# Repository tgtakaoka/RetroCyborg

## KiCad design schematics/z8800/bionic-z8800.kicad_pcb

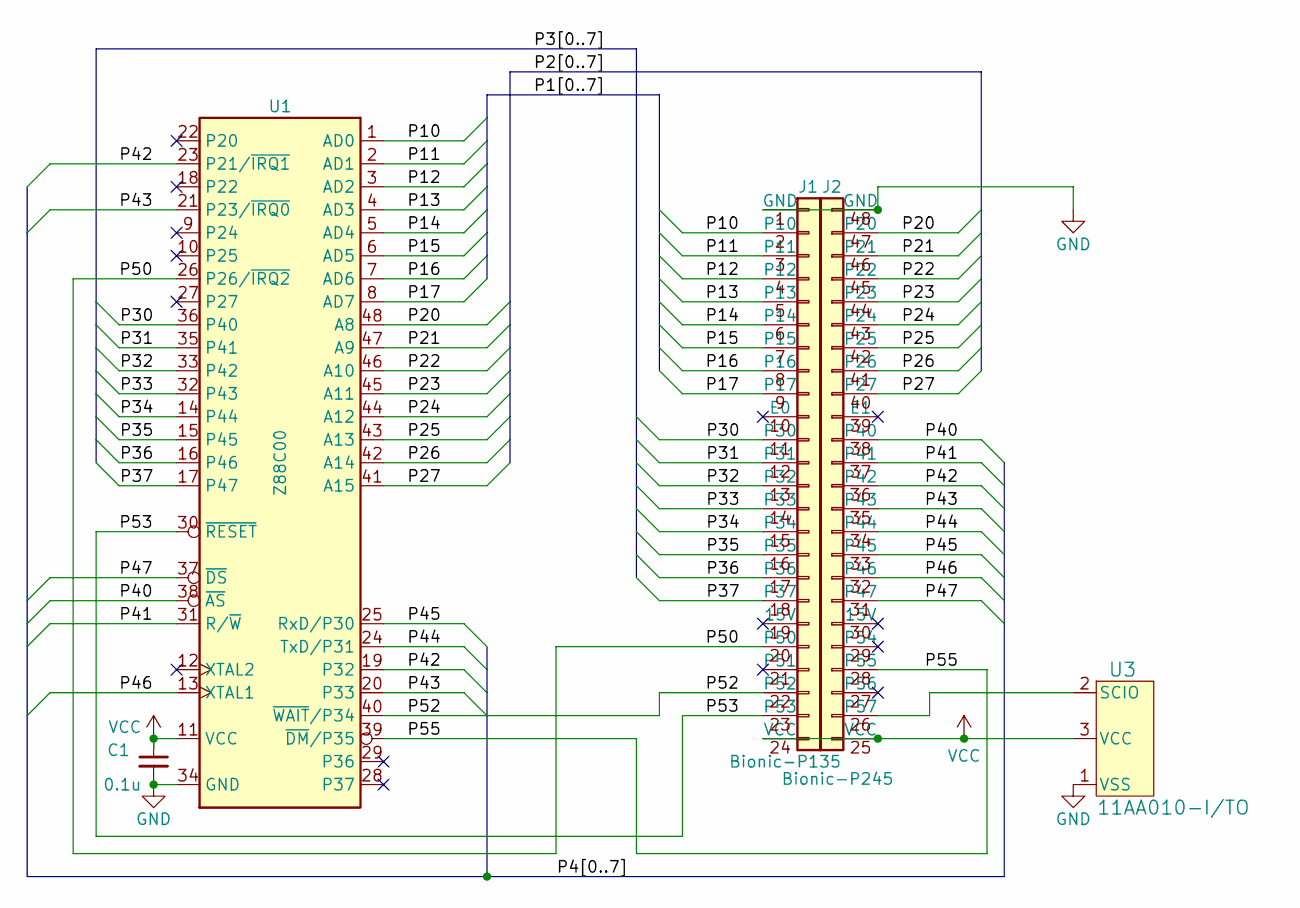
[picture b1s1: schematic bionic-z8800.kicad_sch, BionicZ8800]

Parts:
C1: 0.1u; C_Disc_D3.4mm_W2.1mm_P2.50mm
J1: Bionic-P135; Bionic-P135_Vertical
J2: Bionic-P245; Bionic-P245_Vertical
U1: Z88C00; DIP-48_W15.24mm
U3: 11AA010-I/TO; TO-92_MC_MCH

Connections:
/P10: J1.2 (P10), U1.1 (AD0)
/P11: J1.3 (P11), U1.2 (AD1)
/P12: J1.4 (P12), U1.3 (AD2)
/P13: J1.5 (P13), U1.4 (AD3)
/P14: J1.6 (P14), U1.5 (AD4)
/P15: J1.7 (P15), U1.6 (AD5)
/P16: J1.8 (P16), U1.7 (AD6)
/P17: J1.9 (P17), U1.8 (AD7)
/P20: J2.47 (P20), U1.48 (A8)
/P21: J2.46 (P21), U1.47 (A9)
/P22: J2.45 (P22), U1.46 (A10)
/P23: J2.44 (P23), U1.45 (A11)
/P24: J2.43 (P24), U1.44 (A12)
/P25: J2.42 (P25), U1.43 (A13)
/P26: J2.41 (P26), U1.42 (A14)
/P27: J2.40 (P27), U1.41 (A15)
/P30: J1.11 (P30), U1.36 (P40)
/P31: J1.12 (P31), U1.35 (P41)
/P32: J1.13 (P32), U1.33 (P42)
/P33: J1.14 (P33), U1.32 (P43)
/P34: J1.15 (P34), U1.14 (P44)
/P35: J1.16 (P35), U1.15 (P45)
/P36: J1.17 (P36), U1.16 (P46)
/P37: J1.18 (P37), U1.17 (P47)
/P40: J2.38 (P40), U1.38 (~AS)
/P41: J2.37 (P41), U1.31 (R/~W)
/P42: J2.36 (P42), U1.19 (P32), U1.23 (P21/~IRQ1)
/P43: J2.35 (P43), U1.20 (P33), U1.21 (P23/~IRQ0)
/P44: J2.34 (P44), U1.24 (TxD/P31)
/P45: J2.33 (P45), U1.25 (RxD/P30)
/P46: J2.32 (P46), U1.13 (XTAL1)
/P47: J2.31 (P47), U1.37 (~DS)
/P50: J1.20 (P50), U1.26 (P26/~IRQ2)
/P52: J1.22 (P52), U1.40 (~WAIT/P34)
/P53: J1.23 (P53), U1.30 (~RESET)
/P55: J2.28 (P55), U1.39 (~DM/P35)
GND: C1.2, J1.1 (GND), J2.48 (GND), U1.34 (GND), U3.1 (VSS)
unnamed: J2.26 (P57), U3.2 (SCIO)
VCC: C1.1, J1.24 (VCC), J2.25 (VCC), U1.11 (VCC), U3.3 (VCC)

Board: 2 copper layers, 9 parts (0 on the bottom side), 39 nets, no tracks yet.

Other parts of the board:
MH1, MH2, MH3, MH4: MountingHole_3.2mm_M3

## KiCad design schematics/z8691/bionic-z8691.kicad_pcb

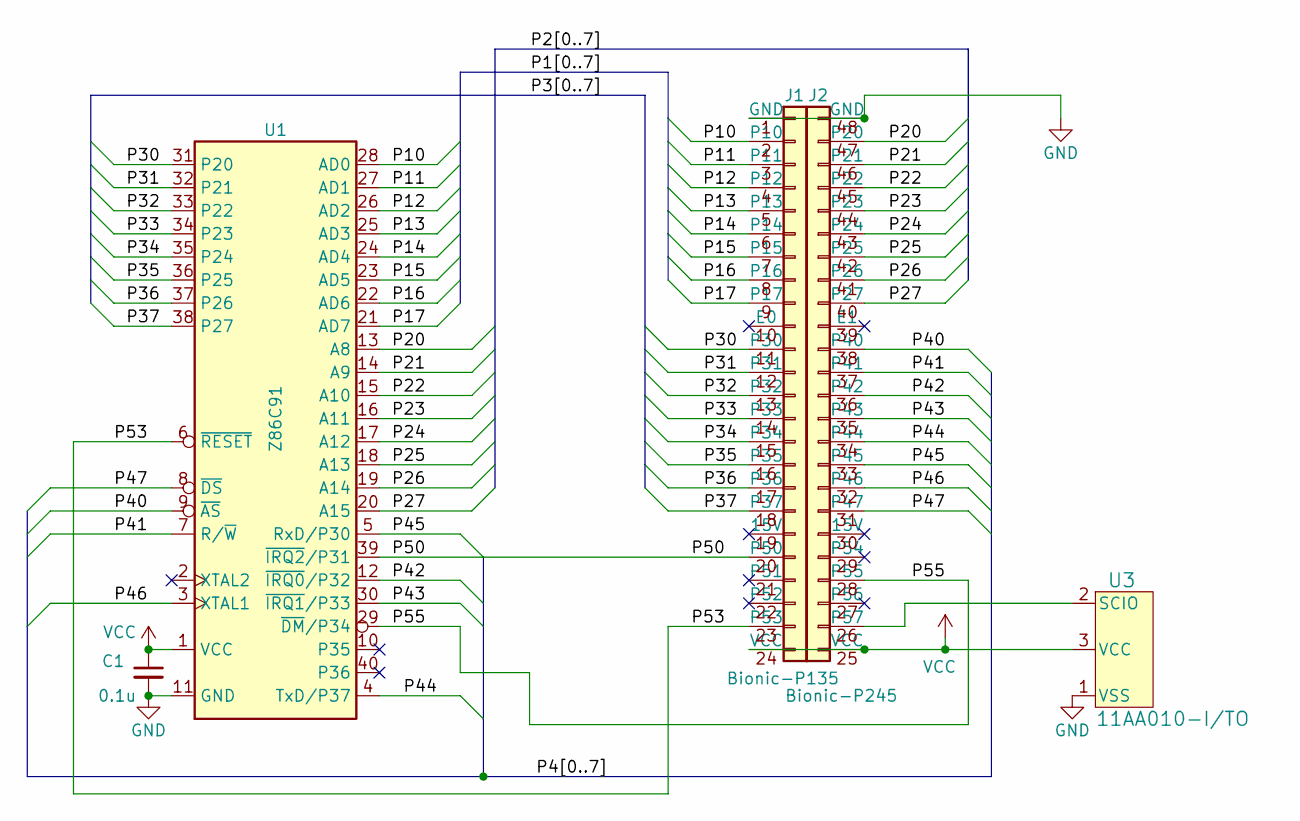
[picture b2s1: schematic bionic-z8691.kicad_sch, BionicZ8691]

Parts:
C1: 0.1u; C_Disc_D3.4mm_W2.1mm_P2.50mm
J1: Bionic-P135; Bionic-P135_Vertical
J2: Bionic-P245; Bionic-P245_Vertical
U1: Z86C91; DIP-40_W15.24mm
U3: 11AA010-I/TO; TO-92_MC_MCH

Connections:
/P10: J1.2 (P10), U1.28 (AD0)
/P11: J1.3 (P11), U1.27 (AD1)
/P12: J1.4 (P12), U1.26 (AD2)
/P13: J1.5 (P13), U1.25 (AD3)
/P14: J1.6 (P14), U1.24 (AD4)
/P15: J1.7 (P15), U1.23 (AD5)
/P16: J1.8 (P16), U1.22 (AD6)
/P17: J1.9 (P17), U1.21 (AD7)
/P20: J2.47 (P20), U1.13 (A8)
/P21: J2.46 (P21), U1.14 (A9)
/P22: J2.45 (P22), U1.15 (A10)
/P23: J2.44 (P23), U1.16 (A11)
/P24: J2.43 (P24), U1.17 (A12)
/P25: J2.42 (P25), U1.18 (A13)
/P26: J2.41 (P26), U1.19 (A14)
/P27: J2.40 (P27), U1.20 (A15)
/P30: J1.11 (P30), U1.31 (P20)
/P31: J1.12 (P31), U1.32 (P21)
/P32: J1.13 (P32), U1.33 (P22)
/P33: J1.14 (P33), U1.34 (P23)
/P34: J1.15 (P34), U1.35 (P24)
/P35: J1.16 (P35), U1.36 (P25)
/P36: J1.17 (P36), U1.37 (P26)
/P37: J1.18 (P37), U1.38 (P27)
/P40: J2.38 (P40), U1.9 (~AS)
/P41: J2.37 (P41), U1.7 (R/~W)
/P42: J2.36 (P42), U1.12 (~IRQ0/P32)
/P43: J2.35 (P43), U1.30 (~IRQ1/P33)
/P44: J2.34 (P44), U1.4 (TxD/P37)
/P45: J2.33 (P45), U1.5 (RxD/P30)
/P46: J2.32 (P46), U1.3 (XTAL1)
/P47: J2.31 (P47), U1.8 (~DS)
/P50: J1.20 (P50), U1.39 (~IRQ2/P31)
/P53: J1.23 (P53), U1.6 (~RESET)
/P55: J2.28 (P55), U1.29 (~DM/P34)
GND: C1.2, J1.1 (GND), J2.48 (GND), U1.11 (GND), U3.1 (VSS)
unnamed: J2.26 (P57), U3.2 (SCIO)
VCC: C1.1, J1.24 (VCC), J2.25 (VCC), U1.1 (VCC), U3.3 (VCC)

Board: 2 copper layers, 9 parts (0 on the bottom side), 38 nets, no tracks yet.

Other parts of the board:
MH1, MH2, MH3, MH4: MountingHole_3.2mm_M3

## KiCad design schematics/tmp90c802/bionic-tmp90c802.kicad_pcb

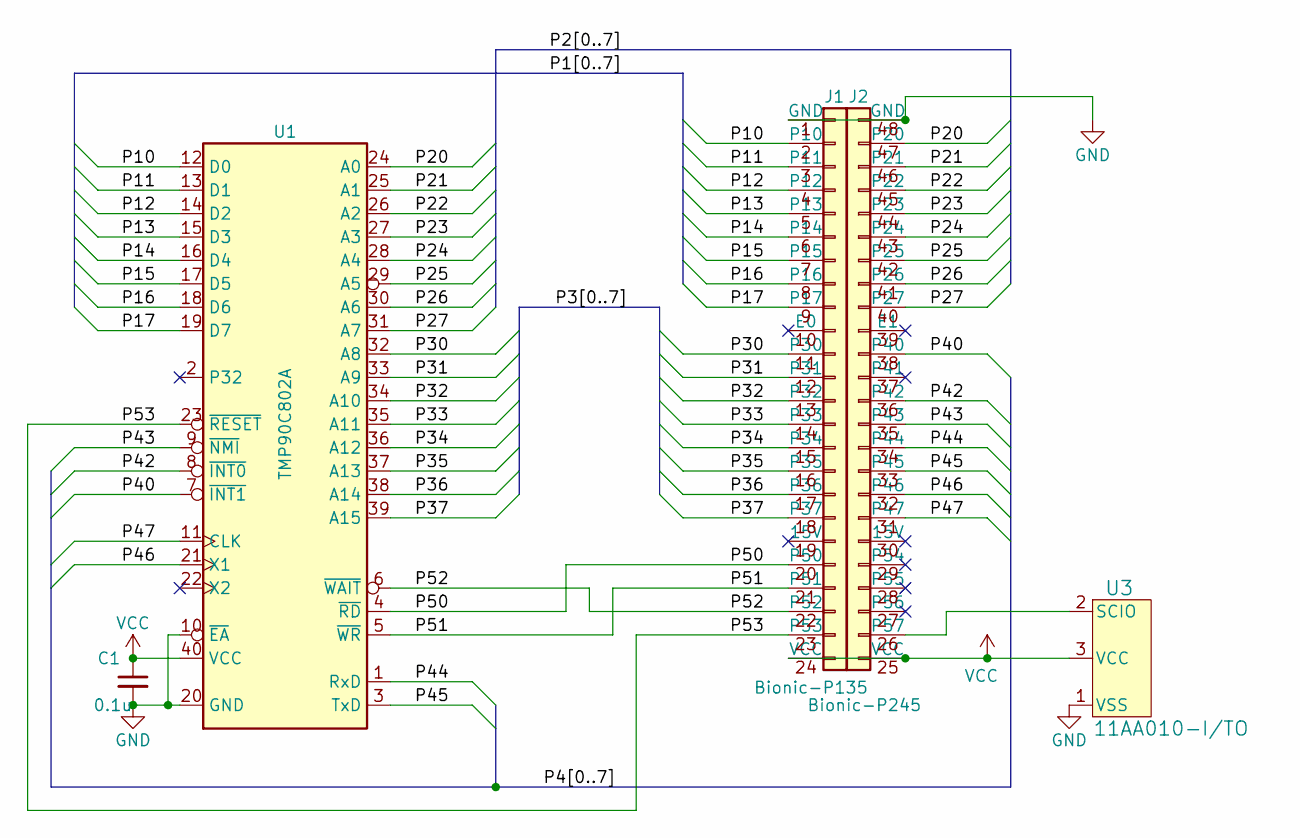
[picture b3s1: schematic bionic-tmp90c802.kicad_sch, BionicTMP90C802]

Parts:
C1: 0.1u; C_Disc_D3.4mm_W2.1mm_P2.50mm
J1: Bionic-P135; Bionic-P135_Vertical
J2: Bionic-P245; Bionic-P245_Vertical
U1: TMP90C802A; DIP-40_W15.24mm
U3: 11AA010-I/TO; TO-92_MC_MCH

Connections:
/P10: J1.2 (P10), U1.12 (D0)
/P11: J1.3 (P11), U1.13 (D1)
/P12: J1.4 (P12), U1.14 (D2)
/P13: J1.5 (P13), U1.15 (D3)
/P14: J1.6 (P14), U1.16 (D4)
/P15: J1.7 (P15), U1.17 (D5)
/P16: J1.8 (P16), U1.18 (D6)
/P17: J1.9 (P17), U1.19 (D7)
/P20: J2.47 (P20), U1.24 (A0)
/P21: J2.46 (P21), U1.25 (A1)
/P22: J2.45 (P22), U1.26 (A2)
/P23: J2.44 (P23), U1.27 (A3)
/P24: J2.43 (P24), U1.28 (A4)
/P25: J2.42 (P25), U1.29 (A5)
/P26: J2.41 (P26), U1.30 (A6)
/P27: J2.40 (P27), U1.31 (A7)
/P30: J1.11 (P30), U1.32 (A8)
/P31: J1.12 (P31), U1.33 (A9)
/P32: J1.13 (P32), U1.34 (A10)
/P33: J1.14 (P33), U1.35 (A11)
/P34: J1.15 (P34), U1.36 (A12)
/P35: J1.16 (P35), U1.37 (A13)
/P36: J1.17 (P36), U1.38 (A14)
/P37: J1.18 (P37), U1.39 (A15)
/P40: J2.38 (P40), U1.7 (~INT1)
/P42: J2.36 (P42), U1.8 (~INT0)
/P43: J2.35 (P43), U1.9 (~NMI)
/P44: J2.34 (P44), U1.1 (RxD)
/P45: J2.33 (P45), U1.3 (TxD)
/P46: J2.32 (P46), U1.21 (X1)
/P47: J2.31 (P47), U1.11 (CLK)
/P50: J1.20 (P50), U1.4 (~RD)
/P51: J1.21 (P51), U1.5 (~WR)
/P52: J1.22 (P52), U1.6 (~WAIT)
/P53: J1.23 (P53), U1.23 (~RESET)
GND: C1.2, J1.1 (GND), J2.48 (GND), U1.10 (~EA), U1.20 (GND), U3.1 (VSS)
unnamed: J2.26 (P57), U3.2 (SCIO)
VCC: C1.1, J1.24 (VCC), J2.25 (VCC), U1.40 (VCC), U3.3 (VCC)

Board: 2 copper layers, 9 parts (0 on the bottom side), 38 nets, no tracks yet.

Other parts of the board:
MH1, MH2, MH3, MH4: MountingHole_3.2mm_M3

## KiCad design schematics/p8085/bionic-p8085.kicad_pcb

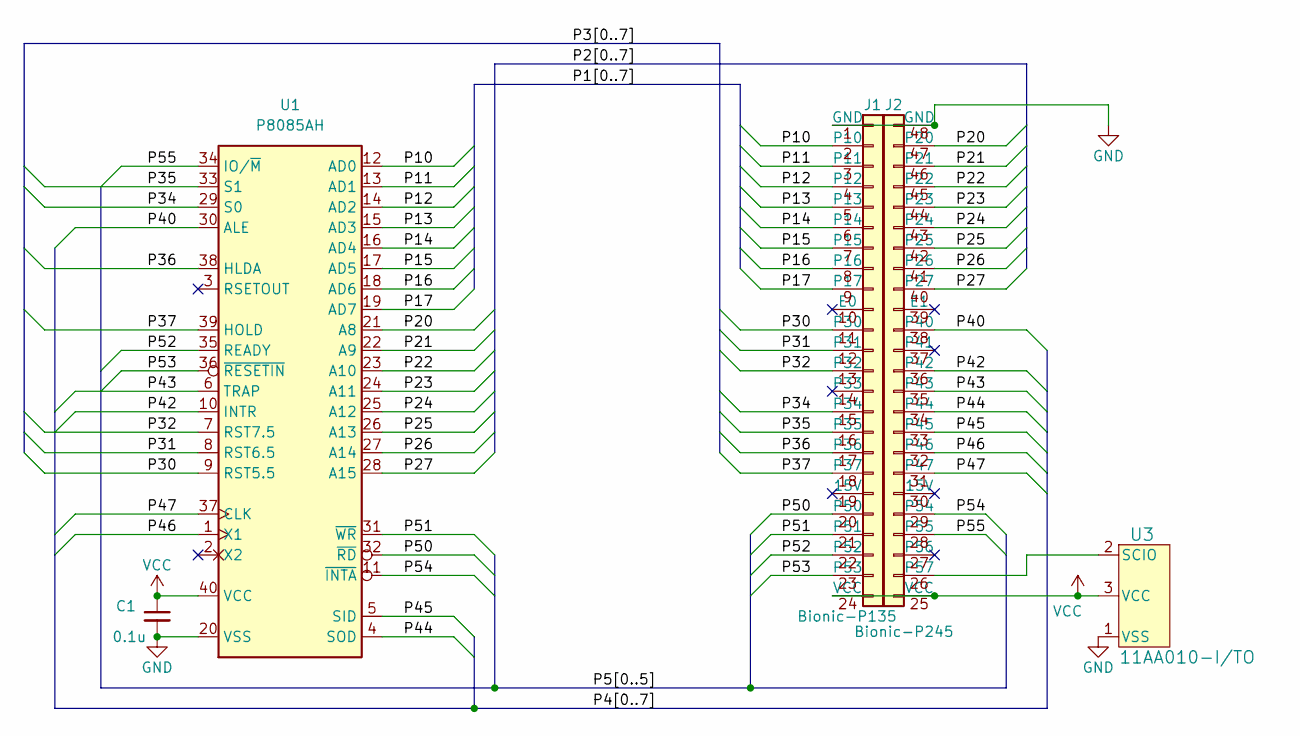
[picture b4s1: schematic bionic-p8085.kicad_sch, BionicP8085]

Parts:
C1: 0.1u; C_Disc_D3.4mm_W2.1mm_P2.50mm
J1: Bionic-P135; Bionic-P135_Vertical
J2: Bionic-P245; Bionic-P245_Vertical
U1: P8085AH; DIP-40_W15.24mm
U3: 11AA010-I/TO; TO-92_MC_MCH

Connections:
/P10: J1.2 (P10), U1.12 (AD0)
/P11: J1.3 (P11), U1.13 (AD1)
/P12: J1.4 (P12), U1.14 (AD2)
/P13: J1.5 (P13), U1.15 (AD3)
/P14: J1.6 (P14), U1.16 (AD4)
/P15: J1.7 (P15), U1.17 (AD5)
/P16: J1.8 (P16), U1.18 (AD6)
/P17: J1.9 (P17), U1.19 (AD7)
/P20: J2.47 (P20), U1.21 (A8)
/P21: J2.46 (P21), U1.22 (A9)
/P22: J2.45 (P22), U1.23 (A10)
/P23: J2.44 (P23), U1.24 (A11)
/P24: J2.43 (P24), U1.25 (A12)
/P25: J2.42 (P25), U1.26 (A13)
/P26: J2.41 (P26), U1.27 (A14)
/P27: J2.40 (P27), U1.28 (A15)
/P30: J1.11 (P30), U1.9 (RST5.5)
/P31: J1.12 (P31), U1.8 (RST6.5)
/P32: J1.13 (P32), U1.7 (RST7.5)
/P34: J1.15 (P34), U1.29 (S0)
/P35: J1.16 (P35), U1.33 (S1)
/P36: J1.17 (P36), U1.38 (HLDA)
/P37: J1.18 (P37), U1.39 (HOLD)
/P40: J2.38 (P40), U1.30 (ALE)
/P42: J2.36 (P42), U1.10 (INTR)
/P43: J2.35 (P43), U1.6 (TRAP)
/P44: J2.34 (P44), U1.4 (SOD)
/P45: J2.33 (P45), U1.5 (SID)
/P46: J2.32 (P46), U1.1 (X1)
/P47: J2.31 (P47), U1.37 (CLK)
/P50: J1.20 (P50), U1.32 (~RD)
/P51: J1.21 (P51), U1.31 (~WR)
/P52: J1.22 (P52), U1.35 (READY)
/P53: J1.23 (P53), U1.36 (~RESETIN)
/P54: J2.29 (P54), U1.11 (~INTA)
/P55: J2.28 (P55), U1.34 (IO/~M)
GND: C1.2, J1.1 (GND), J2.48 (GND), U1.20 (VSS), U3.1 (VSS)
unnamed: J2.26 (P57), U3.2 (SCIO)
VCC: C1.1, J1.24 (VCC), J2.25 (VCC), U1.40 (VCC), U3.3 (VCC)

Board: 2 copper layers, 9 parts (0 on the bottom side), 39 nets, no tracks yet.

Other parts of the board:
MH1, MH2, MH3, MH4: MountingHole_3.2mm_M3

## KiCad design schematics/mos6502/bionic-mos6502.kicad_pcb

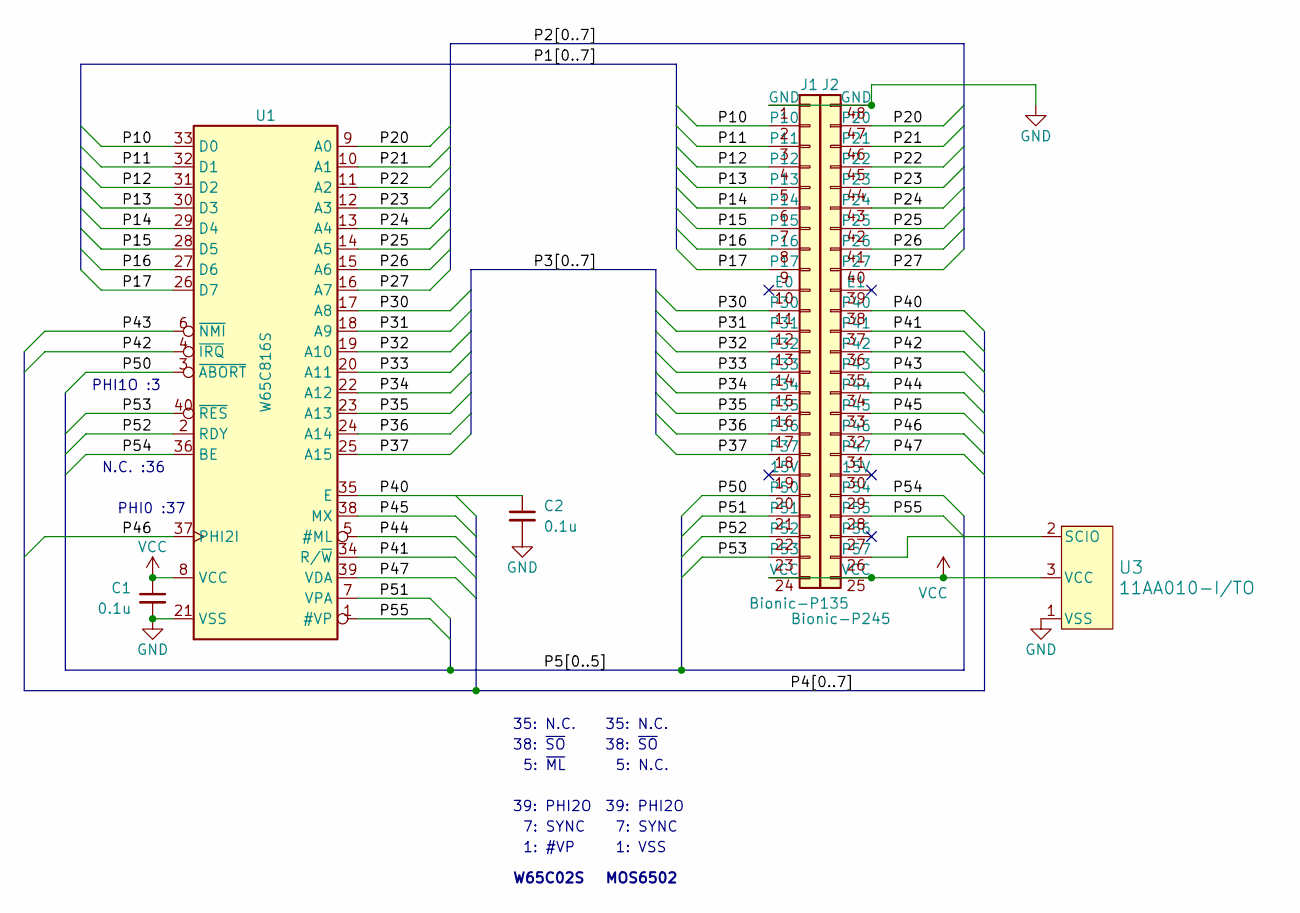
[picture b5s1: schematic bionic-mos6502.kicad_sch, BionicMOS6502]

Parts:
C1, C2: 0.1u; C_Disc_D3.4mm_W2.1mm_P2.50mm
J1: Bionic-P135; Bionic-P135_Vertical
J2: Bionic-P245; Bionic-P245_Vertical
U1: W65C816S; DIP-40_W15.24mm
U3: 11AA010-I/TO; TO-92_MC_MCH

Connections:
/P10: J1.2 (P10), U1.33 (D0)
/P11: J1.3 (P11), U1.32 (D1)
/P12: J1.4 (P12), U1.31 (D2)
/P13: J1.5 (P13), U1.30 (D3)
/P14: J1.6 (P14), U1.29 (D4)
/P15: J1.7 (P15), U1.28 (D5)
/P16: J1.8 (P16), U1.27 (D6)
/P17: J1.9 (P17), U1.26 (D7)
/P20: J2.47 (P20), U1.9 (A0)
/P21: J2.46 (P21), U1.10 (A1)
/P22: J2.45 (P22), U1.11 (A2)
/P23: J2.44 (P23), U1.12 (A3)
/P24: J2.43 (P24), U1.13 (A4)
/P25: J2.42 (P25), U1.14 (A5)
/P26: J2.41 (P26), U1.15 (A6)
/P27: J2.40 (P27), U1.16 (A7)
/P30: J1.11 (P30), U1.17 (A8)
/P31: J1.12 (P31), U1.18 (A9)
/P32: J1.13 (P32), U1.19 (A10)
/P33: J1.14 (P33), U1.20 (A11)
/P34: J1.15 (P34), U1.22 (A12)
/P35: J1.16 (P35), U1.23 (A13)
/P36: J1.17 (P36), U1.24 (A14)
/P37: J1.18 (P37), U1.25 (A15)
/P40: C2.1, J2.38 (P40), U1.35 (E)
/P41: J2.37 (P41), U1.34 (R/~W)
/P42: J2.36 (P42), U1.4 (~IRQ)
/P43: J2.35 (P43), U1.6 (~NMI)
/P44: J2.34 (P44), U1.5 (#ML)
/P45: J2.33 (P45), U1.38 (MX)
/P46: J2.32 (P46), U1.37 (PHI2I)
/P47: J2.31 (P47), U1.39 (VDA)
/P50: J1.20 (P50), U1.3 (~ABORT)
/P51: J1.21 (P51), U1.7 (VPA)
/P52: J1.22 (P52), U1.2 (RDY)
/P53: J1.23 (P53), U1.40 (~RES)
/P54: J2.29 (P54), U1.36 (BE)
/P55: J2.28 (P55), U1.1 (#VP)
GND: C1.2, C2.2, J1.1 (GND), J2.48 (GND), U1.21 (VSS), U3.1 (VSS)
unnamed: J2.26 (P57), U3.2 (SCIO)
VCC: C1.1, J1.24 (VCC), J2.25 (VCC), U1.8 (VCC), U3.3 (VCC)

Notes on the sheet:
N.C. :36
PHI0 :37
35: N.C.
MOS6502
5: N.C.
W65C02S
7: SYNC
PHI1O :3
39: PHI2O
1: VSS
5: ~{ML}
1: #VP
38: ~{SO}

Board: 2 copper layers, 10 parts (0 on the bottom side), 41 nets, no tracks yet.

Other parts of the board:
MH1, MH2, MH3, MH4: MountingHole_3.2mm_M3

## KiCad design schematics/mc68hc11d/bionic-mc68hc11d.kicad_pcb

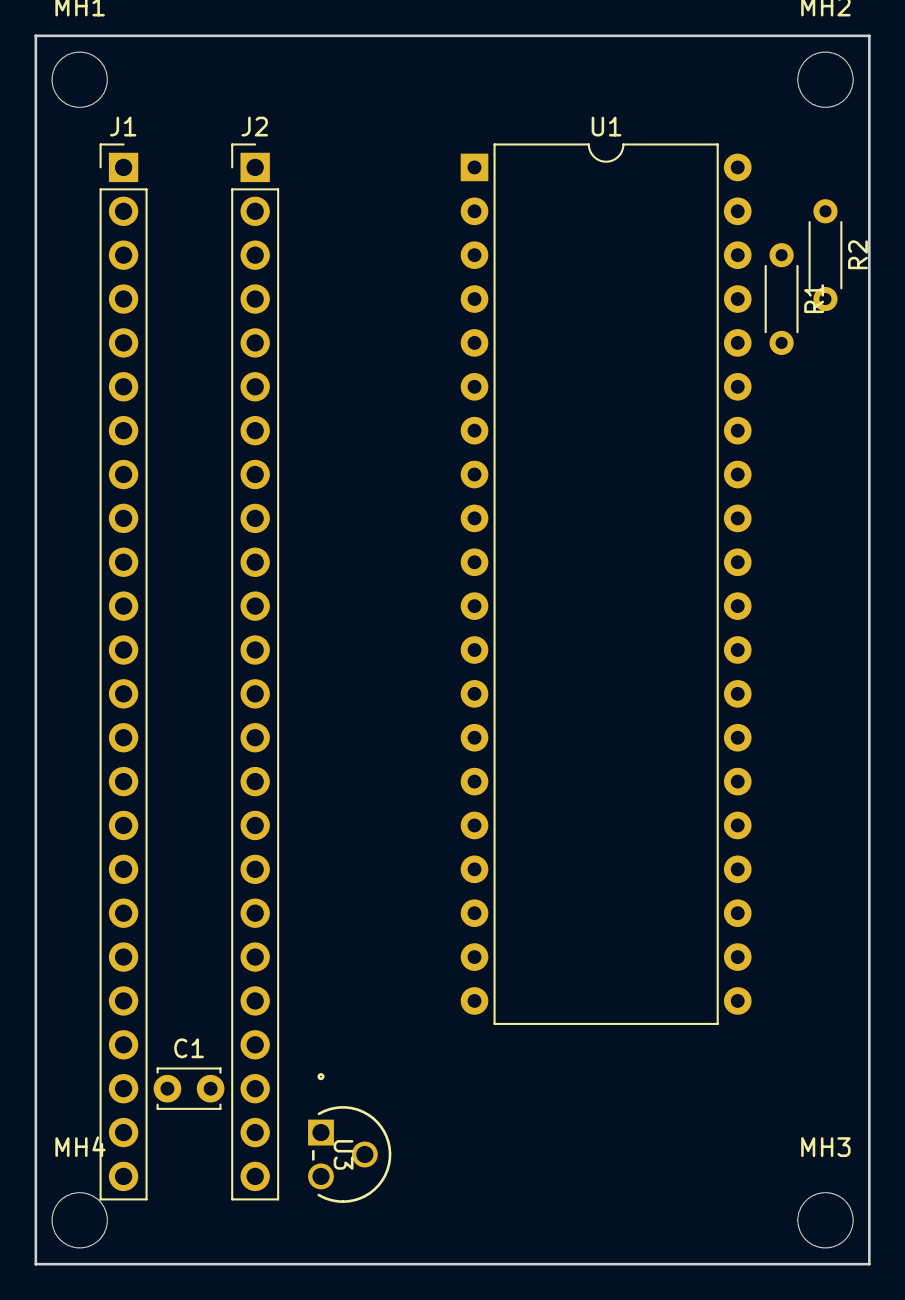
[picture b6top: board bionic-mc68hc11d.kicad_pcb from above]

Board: 2 copper layers, 48.3 x 71.1 mm, 11 parts (0 on the bottom side), 40 nets, no tracks yet.

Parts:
C1: 0.1u; C_Disc_D3.4mm_W2.1mm_P2.50mm
J1: Bionic-P135; Bionic-P135_Vertical
J2: Bionic-P245; Bionic-P245_Vertical
MH1, MH2, MH3, MH4: MountingHole_3.2mm_M3
R1, R2: 10k; R_Axial_DIN0204_L3.6mm_D1.6mm_P5.08mm_Horizontal
U1: MC68HC11D0P; DIP-40_W15.24mm
U3: 11AA010-I/TO; TO-92_MC_MCH

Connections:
/P10: J1.2 (P10), U1.2 (AD0)
/P11: J1.3 (P11), U1.3 (AD1)
/P12: J1.4 (P12), U1.4 (AD2)
/P13: J1.5 (P13), U1.5 (AD3)
/P14: J1.6 (P14), U1.6 (AD4)
/P15: J1.7 (P15), U1.7 (AD5)
/P16: J1.8 (P16), U1.8 (AD6)
/P17: J1.9 (P17), U1.9 (AD7)
/P20: J2.47 (P20), U1.35 (A8)
/P21: J2.46 (P21), U1.34 (A9)
/P22: J2.45 (P22), U1.33 (A10)
/P23: J2.44 (P23), U1.32 (A11)
/P24: J2.43 (P24), U1.31 (A12)
/P25: J2.42 (P25), U1.30 (A13)
/P26: J2.41 (P26), U1.29 (A14)
/P27: J2.40 (P27), U1.28 (A15)
/P30: J1.11 (P30), U1.27 (PA0)
/P31: J1.12 (P31), U1.26 (PA1)
/P32: J1.13 (P32), U1.25 (PA2)
/P33: J1.14 (P33), U1.24 (PA3)
/P34: J1.15 (P34), U1.17 (MISO/PD2)
/P35: J1.16 (P35), U1.18 (MOSI/PD3)
/P36: J1.17 (P36), U1.19 (SCK/PD4)
/P37: J1.18 (P37), U1.20 (~SS/PD5)
/P40: J2.38 (P40), U1.12 (AS)
/P41: J2.37 (P41), U1.11 (R/~W)
/P42: J2.36 (P42), U1.14 (~IRQ)
/P43: J2.35 (P43), U1.10 (~XIRQ)
/P44: J2.34 (P44), U1.16 (TxD/PD1)
/P45: J2.33 (P45), U1.15 (RxD/PD0)
/P46: J2.32 (P46), U1.39 (EXTAL)
/P47: J2.31 (P47), U1.38 (E)
/P50: J1.20 (P50), R2.2, U1.37 (MODA/~LIR)
/P51: J1.21 (P51), R1.2, U1.36 (MODB)
/P53: J1.23 (P53), U1.13 (~RESET)
/P54: J2.29 (P54), U1.23 (PA5)
/P55: J2.28 (P55), U1.22 (PA7)
GND: C1.2, J1.1 (GND), J2.48 (GND), U1.1 (VSS), U3.1 (VSS)
unnamed: J2.26 (P57), U3.2 (SCIO)
VCC: C1.1, J1.24 (VCC), J2.25 (VCC), R1.1, R2.1, U1.21 (VDD), U3.3 (VCC)

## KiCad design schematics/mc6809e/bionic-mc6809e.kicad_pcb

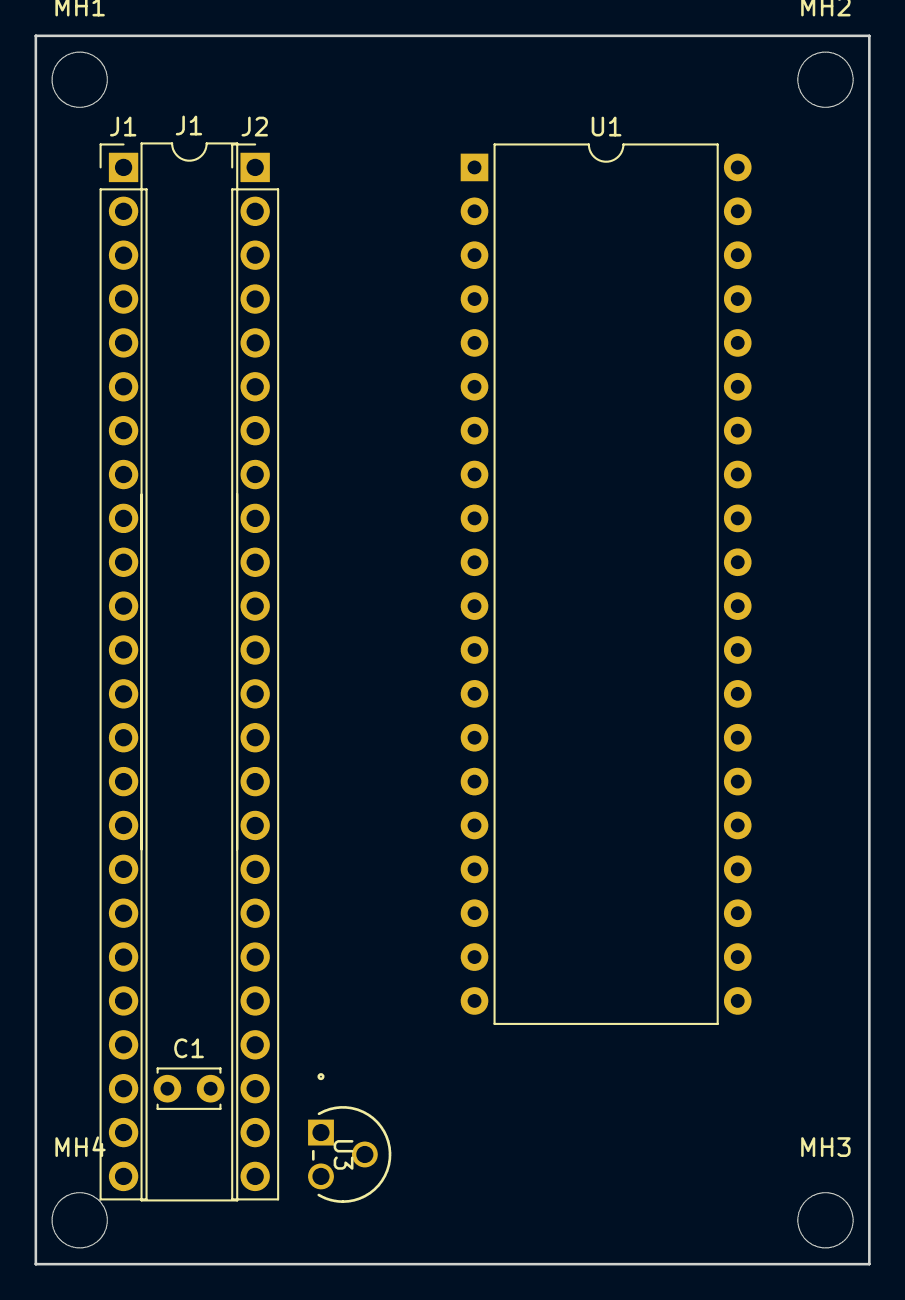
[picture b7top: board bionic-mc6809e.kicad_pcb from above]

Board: 2 copper layers, 48.3 x 71.1 mm, 10 parts (0 on the bottom side), 41 nets, no tracks yet.

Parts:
C1: 0.1u; C_Disc_D3.4mm_W2.1mm_P2.50mm
J1: BionicConnector; DIP-48_W7.62mm
J1#2: Bionic-P135; Bionic-P135_Vertical
J2: Bionic-P245; Bionic-P245_Vertical
MH1, MH2, MH3, MH4: MountingHole_3.2mm_M3
U1: MC6809EP; DIP-40_W15.24mm
U3: 11AA010-I/TO; TO-92_MC_MCH

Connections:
/P10: J1.2 (P10), J1#2.2 (P10), U1.31 (D0)
/P11: J1.3 (P11), J1#2.3 (P11), U1.30 (D1)
/P12: J1.4 (P12), J1#2.4 (P12), U1.29 (D2)
/P13: J1.5 (P13), J1#2.5 (P13), U1.28 (D3)
/P14: J1.6 (P14), J1#2.6 (P14), U1.27 (D4)
/P15: J1.7 (P15), J1#2.7 (P15), U1.26 (D5)
/P16: J1.8 (P16), J1#2.8 (P16), U1.25 (D6)
/P17: J1.9 (P17), J1#2.9 (P17), U1.24 (D7)
/P20: J1.47 (P20), J2.47 (P20), U1.8 (A0)
/P21: J1.46 (P21), J2.46 (P21), U1.9 (A1)
/P22: J1.45 (P22), J2.45 (P22), U1.10 (A2)
/P23: J1.44 (P23), J2.44 (P23), U1.11 (A3)
/P24: J1.43 (P24), J2.43 (P24), U1.12 (A4)
/P25: J1.42 (P25), J2.42 (P25), U1.13 (A5)
/P26: J1.41 (P26), J2.41 (P26), U1.14 (A6)
/P27: J1.40 (P27), J2.40 (P27), U1.15 (A7)
/P30: J1.11 (P30), J1#2.11 (P30), U1.16 (A8)
/P31: J1.12 (P31), J1#2.12 (P31), U1.17 (A9)
/P32: J1.13 (P32), J1#2.13 (P32), U1.18 (A10)
/P33: J1.14 (P33), J1#2.14 (P33), U1.19 (A11)
/P34: J1.15 (P34), J1#2.15 (P34), U1.20 (A12)
/P35: J1.16 (P35), J1#2.16 (P35), U1.21 (A13)
/P36: J1.17 (P36), J1#2.17 (P36), U1.22 (A14)
/P37: J1.18 (P37), J1#2.18 (P37), U1.23 (A15)
/P40: J1.38 (P40), J2.38 (P40), U1.40 (~HALT)
/P41: J1.37 (P41), J2.37 (P41), U1.32 (R/~W)
/P42: J1.36 (P42), J2.36 (P42), U1.3 (~IRQ)
/P43: J1.35 (P43), J2.35 (P43), U1.2 (~NMI)
/P44: J1.34 (P44), J2.34 (P44), U1.33 (BUSY)
/P45: J1.33 (P45), J2.33 (P45), U1.4 (~FIRQ)
/P46: J1.32 (P46), J2.32 (P46), U1.34 (E)
/P47: J1.31 (P47), J2.31 (P47), U1.35 (Q)
/P50: J1.20 (P50), J1#2.20 (P50), U1.36 (AVMA)
/P51: J1.21 (P51), J1#2.21 (P51), U1.5 (BS)
/P52: J1.22 (P52), J1#2.22 (P52), U1.38 (LIC)
/P53: J1.23 (P53), J1#2.23 (P53), U1.37 (~RESET)
/P54: J1.29 (P54), J2.29 (P54), U1.39 (TSC)
/P55: J1.28 (P55), J2.28 (P55), U1.6 (BA)
GND: C1.2, J1.1 (GND), J1.48 (GND), J1#2.1 (GND), J2.48 (GND), U1.1 (VSS), U3.1 (VSS)
unnamed: J2.26 (P57), U3.2 (SCIO)
VCC: C1.1, J1.24 (VCC), J1.25 (VCC), J1#2.24 (VCC), J2.25 (VCC), U1.7 (VCC), U3.3 (VCC)

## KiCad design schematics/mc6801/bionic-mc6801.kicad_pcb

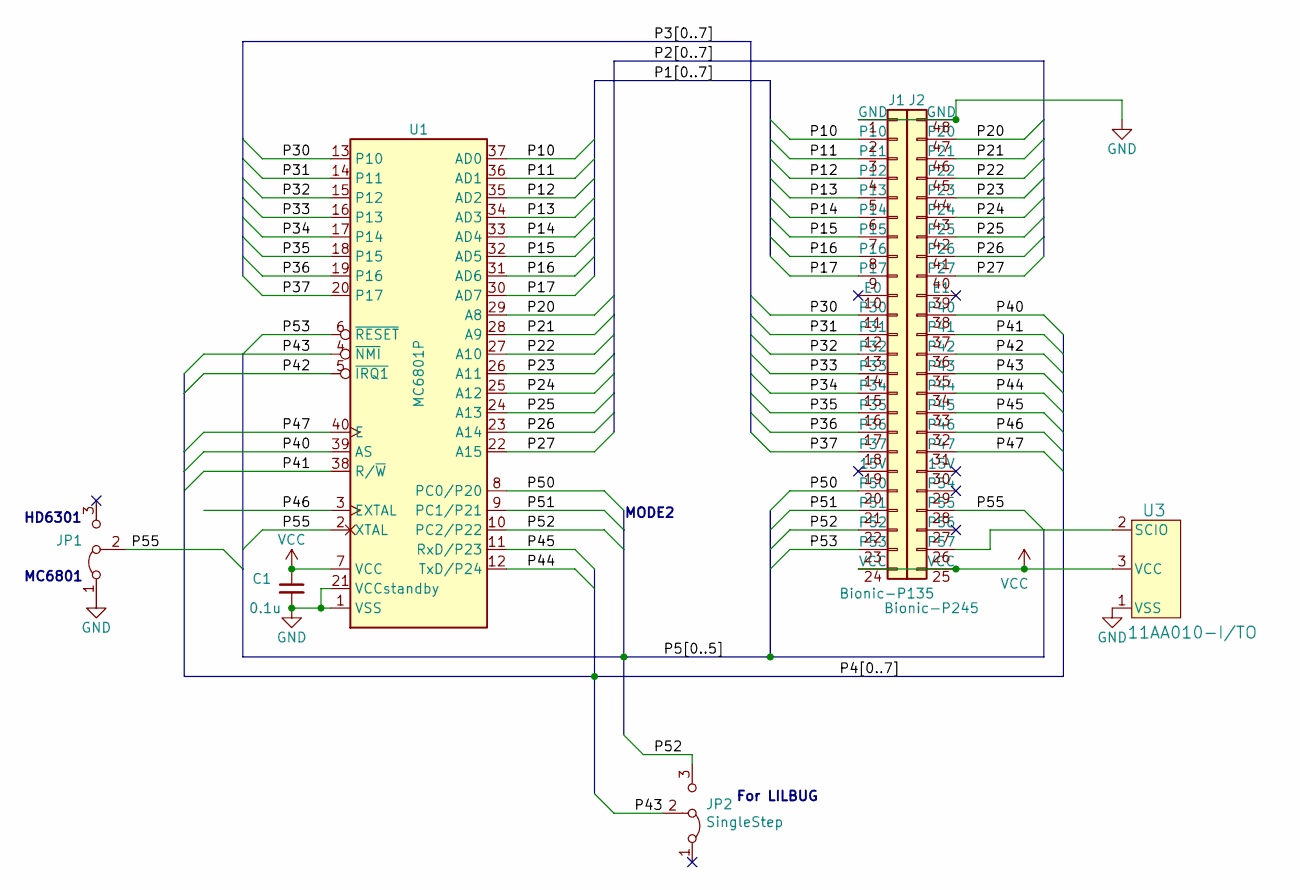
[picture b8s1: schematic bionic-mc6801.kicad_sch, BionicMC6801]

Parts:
C1: 0.1u; C_Disc_D3.4mm_W2.1mm_P2.50mm
J1: Bionic-P135; Bionic-P135_Vertical
J2: Bionic-P245; Bionic-P245_Vertical
JP1: MC6801; PinHeader_1x03_P2.54mm_Vertical
JP2: SingleStep; PinHeader_1x03_P2.54mm_Vertical
U1: MC6801P; DIP-40_W15.24mm
U3: 11AA010-I/TO; TO-92_MC_MCH

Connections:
/P10: J1.2 (P10), U1.37 (AD0)
/P11: J1.3 (P11), U1.36 (AD1)
/P12: J1.4 (P12), U1.35 (AD2)
/P13: J1.5 (P13), U1.34 (AD3)
/P14: J1.6 (P14), U1.33 (AD4)
/P15: J1.7 (P15), U1.32 (AD5)
/P16: J1.8 (P16), U1.31 (AD6)
/P17: J1.9 (P17), U1.30 (AD7)
/P20: J2.47 (P20), U1.29 (A8)
/P21: J2.46 (P21), U1.28 (A9)
/P22: J2.45 (P22), U1.27 (A10)
/P23: J2.44 (P23), U1.26 (A11)
/P24: J2.43 (P24), U1.25 (A12)
/P25: J2.42 (P25), U1.24 (A13)
/P26: J2.41 (P26), U1.23 (A14)
/P27: J2.40 (P27), U1.22 (A15)
/P30: J1.11 (P30), U1.13 (P10)
/P31: J1.12 (P31), U1.14 (P11)
/P32: J1.13 (P32), U1.15 (P12)
/P33: J1.14 (P33), U1.16 (P13)
/P34: J1.15 (P34), U1.17 (P14)
/P35: J1.16 (P35), U1.18 (P15)
/P36: J1.17 (P36), U1.19 (P16)
/P37: J1.18 (P37), U1.20 (P17)
/P40: J2.38 (P40), U1.39 (AS)
/P41: J2.37 (P41), U1.38 (R/~W)
/P42: J2.36 (P42), U1.5 (~IRQ1)
/P43: J2.35 (P43), JP2.2 (C), U1.4 (~NMI)
/P44: J2.34 (P44), U1.12 (TxD/P24)
/P45: J2.33 (P45), U1.11 (RxD/P23)
/P46: J2.32 (P46), U1.3 (EXTAL)
/P47: J2.31 (P47), U1.40 (E)
/P50: J1.20 (P50), U1.8 (PC0/P20)
/P51: J1.21 (P51), U1.9 (PC1/P21)
/P52: J1.22 (P52), JP2.3 (B), U1.10 (PC2/P22)
/P53: J1.23 (P53), U1.6 (~RESET)
/P55: J2.28 (P55), JP1.2 (C), U1.2 (XTAL)
GND: C1.2, J1.1 (GND), J2.48 (GND), JP1.1 (A), U1.1 (VSS), U1.21 (VCCstandby), U3.1 (VSS)
unnamed: J2.26 (P57), U3.2 (SCIO)
VCC: C1.1, J1.24 (VCC), J2.25 (VCC), U1.7 (VCC), U3.3 (VCC)

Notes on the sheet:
MODE2
For LILBUG
HD6301
MC6801

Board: 2 copper layers, 11 parts (0 on the bottom side), 40 nets, no tracks yet.

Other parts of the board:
MH1, MH2, MH3, MH4: MountingHole_3.2mm_M3

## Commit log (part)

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2021-10-28 [HD6309E] Update Arduino IDE setting comment
2021-10-28 Add retro CPU's pin out
    - CDP1802
    - HD6301V/HD6303R
    - INS8060
    - INS8070
    - MC68008P
    - MC6800
2021-10-28 [CyborgZ84C00] update libcli 1.0.3
2021-10-28 [CyborgHD6309E] update libcli 1.0.3
2021-10-28 Add PlatformIO configurations
2021-10-28 Restore CyborgHD6309E/Prototype3 code
2021-10-28 Add NSC800N pin out
    NSC800N has Z80 software architecture and 8051-like hardware signals.
2021-10-28 Add MC6802/MC6808 pin out
2021-10-28 [CyborgZ84C00] update debugger code
2021-10-28 [CyborgHD6309E] Prototype3 modify pins map
2021-10-28 [CyborgHD6309E] Add debug status to Signals
2021-10-28 [CyborgHD6309E] Consolidate Prototype3/4 debugger
2021-10-28 [CyborgHD6309E] Prorotype5 debugger
2021-10-28 [CyborgHD6309E] Add Signals.advancedValidMemoryAddress
2021-10-28 [BionicHD6303] Add clock generator test running on Teensy 3.5
2021-10-28 [CyborgHD6309E] Reorganize Prototype4
2021-10-28 [CyborgHD6309E] Fix register endian handling
    Values in captured buffer from stack frame is little endian which is
    accidentally equals to AVR's endianess.
2021-10-28 [CyborgHD6309E] Refactor Pins.cycle()
    Now HD6309's native mode works correctly.
2021-10-28 [CyborgZ84C00] Update pin mapping
2021-10-28 [CyborgHD6309E] Consolidate Pins.execInst/captureReads/captureWrites
2021-10-28 [CyborgHD6309E] Add Prototype5 cgen6309e-test
2021-10-28 Add DIP definitions
    This TOML files are input for
    https://github.com/tgtakaoka/dip
2021-10-28 [CyborgZ84C00] Add cgenz80-test
2021-10-28 [CyborgHD6309E] Batch capture and print
2021-10-28 Add Teensy 3.5/4.1, Nano Every pin out
2021-10-28 [CyborgHD6309E] Restore Prototype3
2021-10-28 [CyborgHD6309E] Update dependent library version
    - libcli 1.2.1
    - libasm 1.6.16
2021-10-28 [CyborgHD6309E] Prototype4/cgen6309e PlatformIO supported
2021-10-28 [CyborgHD6309E] Update Prototype4 pins to compatible with Prototype5
2021-10-28 [CyborgHD6309E] Update libcli/libasm version
2021-10-28 [CyborgZ84C00] Update schematics symbols
2021-10-28 [CyborgHD6309E] Rename Status to Signals
2021-10-28 [CyborgHD6309E] Separate Status from Pins.
2021-10-28 [CyborgHD6309E] Update Prototype3 to libcli 1.0.4
2021-10-29 [BionicMC6803] Add debbugger
2021-10-29 [BionicMC6803] Add MC6850 emulation
2021-10-29 [BionicMc6803] Refactor SciHandler
2021-10-29 [BionicHD6303] Add schematic
2021-10-29 [BionicMc6803] Refactor Mc6850 emulator
2021-10-29 [BionicHD6303] Replace MC6803 name with HD6303
2021-10-29 [BionicMC6803/BionicHD6303] Update samples
2021-10-29 [CyborgHD6309E] Update debugger
2021-10-29 [CyborgHD6309E] Update sample
2021-10-29 [BionicMC146805E] Add schematics
2021-10-29 [BionicMC146805E] Copy debugger from BionicMC6803
2021-10-29 [BionicMC146805E] Add MC6850 sample
2021-10-29 [BionicMC6802] Copy debugger from MC6803
2021-10-29 [BionicMC6802] Fixup for MC6802/MC6808
2021-10-29 [BionicMC6802] Add MC6850 ACIA samples
2021-11-08 [BionicMC6803] Update to BionicBase/Teensy35 configuration
2021-11-08 [BionicMC146805E] Update to BionicBase/Teensy35 configuration
2021-11-08 [BionicMC6802] Update to BionicBase/Teensy35 configuration
2021-11-28 [BionicMC6803] Mezzanine board
2021-11-28 [BionicBase] Add schematics
2021-11-28 [BionicHD6303] Add Teensy 4.1 breadboard and mezzanine
2021-11-28 [BionicMC6809] Fixup for MC6809
2021-11-28 [BionicMC6800] Add Teensy 4.1 breadboard and mezzanine
2021-11-28 [BionicMC6809] Add schematics
2021-11-28 [BionicMC6800] Copy from BionicMC6802
2021-11-28 [BionicMC6803] Change config.h for MC6803
2021-11-28 [BionicMC146805E] Add Teensy 4.1 breadboard and mezzanine
2021-11-28 [BionicMC6803] Copy debugger from BionicHD6303
2021-11-28 [BionicMC6803] Tune bus cycle
2021-11-28 [BionicMC6802] Add Teensy 4.1 breadboard and mezzanine
2021-11-28 [Teensy4.1] Do not use TEENSY_OPT_FASTEST_LTO
2021-11-28 [BionicHD6303] Use NMI for step and eliminates cycles table
2021-11-28 [BionicMC6809E] Add Teensy 4.1 breadboard and mezzanine
2021-11-28 [BionicMC6802] Mezzanine board
2021-11-29 [BionicMC68HC11D] Add samples from BionicMC6801
2021-11-29 [BionicMC68HC11D] Refactor samples to use 6811 instructions
2021-11-29 [BionicMC68HC11D] Add schematics
2021-12-04 [BionicMC6800] Fix to drive DBE
2021-12-04 [BionicMC146805E] Tune bus cycle
    - Teensy 4.1: OSC1 ~ 4MHz, AS/DS ~ 800kHz
    - Teensy 3.5: OSC1 ~ 1MHz, AS/DS ~ 200kHz
2021-12-04 [BionicMC6801] Tune bus cycle
    - Teensy 4.1: EXTAL ~3.5MHz, E ~880kHz
    - Teensy 3.5: EXTAL ~1.2MHz, E ~300kHz
2021-12-06 [BionicMC6809] Tune bus cycle
    - Teensy 4.1: Q/E ~ 780kHz
    - Teensy 3.5: Q/E ~ 250kHz
2021-12-06 [BionicMC6809E] Tune bus cycle
    - Teensy 4.1: Q/E ~ 1.0MHz
    - Teensy 3.5: Q/E ~ 230kHz
2021-12-06 [BionicMC6809] Support HD6309
2021-12-12 [BionicMC6809E] Support HD6309 native mode
2021-12-12 [BionicMC6809] Support HD6309 native mode
2021-12-12 [CyborgHD6309E] Introduce Memory class
2021-12-12 [CyborgHD6309E] Refactor print out
2021-12-12 [CyborgHD6309E] Include real MPU name in version name
2022-01-30 [CyborgHD6309E] Update mc6805.cpp to libcli 1.2.3
2022-01-30 [CyborgHD6309E] Improve 'P' and 'I' commands
2022-01-30 [CyborgHD6309E] Fix echo.asm not to use BITA
    With unknown reason, HD6309E BITA got wrong result.
2022-02-01 [BionicMC6809] Refactor set register command
2022-02-01 [BionicMC6802] Refactor set register command
2022-02-01 [BionicMC146805E] Refactor set register command
2022-02-01 [BionicINS8070] Copy debugger from BionicMC6801
2022-02-01 [BionicINS8070] Add samples
2022-02-01 [BionicMC68HC11D] Refactor set register command
2022-02-01 [BionicINS8070] Add schematics
2022-02-01 [BionicMOS6502] Add bypass capaciters to prevent sprious #NMI
2022-02-01 [BionicMC6809/MC6809E] Add ASSIST09 binary
2022-02-01 [BionicMOS6502] Fixup for MOS6502 and variants
    TODO: support native mode of W65C816S.
2022-02-01 [BionicMC6809/MC6809E] Add Microsoft Basic binary
2022-02-01 [BionicMC6800/MC6802] Add MIKBUG binary
2022-02-01 [BionicMC146805E] Add ASSIST05 binary
2022-02-01 [BionicMC6800/MC6802] Add Microsoft Basic binary and patch
2022-02-01 [BionicMC6801] Add LILBUG binary
2022-02-12 [BionicINS8070] Add INS8073 ROM binary and patch
2022-02-12 [BionicINS8070] Add INS8070 software UART handler
    NSC Tiny Basic (INS8073) implements console using F1 as #TxD and SA as
    RxD.
2022-02-12 [BionicINS8060] Copy debugger from INS8070
2022-02-12 Fix typo
2022-02-12 [BionicINS8060] Fixup for INS8060
2022-02-12 6502
2022-02-12 [BionicINS8070] Move instruction fetch predicate to Signals
2022-02-12 [BionicCDP1802] Add RCA Basic 3 and sample
    From http://www.sunrise-ev.com/1802.htm
    - I)o Bitbang
    - L)oad MCBASCI3.HEX
    - R)eset and Go)
    - Type carriage return key, and type 'C' for cold start
2022-02-12 [Regs] Move disassemble code from Commands
2022-02-12 [Regs] Move assemble code from Commands
2022-02-12 [BionicCDP1802] Fixup for CDP1802
2022-02-12 [CyborgHD6309E] Make Prototype5 final
2022-02-12 [MC6850] Add reset()
2022-02-12 [BionicMC6800/BionicMC6802] Fix bus signal print
2022-02-12 Fix interrupt sample code
2022-02-12 [BionicINS8060] Add Floating point Basic and patch
    From https://www.dos4ever.com/SCMP/SCMP.html#fpoint
    - I)o Bitbang 1200
    - L)oad NIBL.hex
    - L)oad nibl1200bps.hex
    - L)oad FBASL.hex
    - L)oad FBASH.hex
2022-02-12 Fix char signess issue
2022-02-12 [BionicCDP1802] Add bitbang software UART handler
2022-02-12 [BionicCDP1802] Add sample code
2022-02-12 [BionicCDP1802] Disassemble bus cycles when halt or IDL
2022-02-12 [BionicMOS6502] Disassemble bus cycles when halt
2022-07-18 Add P8095BH pin out
2022-07-18 [BionicP8095] Add schematics
2022-07-18 [BionicP8086/P8088] Add V30/V20 chips to library
2022-07-18 Add SCN2650 pin out
2022-10-26 Migrate to KiCad 6.0
2023-03-16 [BionicMC6800/BionicMC6802] Add MB8861/MB8870 detection
2023-03-16 [BionicMOS6502] Fix LDX operand overlfow
2023-03-16 Satisfy Electrical Rules Checker
2023-04-19 [BionicP8085] Copy debugger from BionicINS8070
2023-05-18 Use CPU specific literal syntax
2023-05-18 [BionicP8085] Add i8251 USART emulator
2023-05-18 [BioniocP8085] Add SIO sample
2023-06-23 [BionicZ8691] Copy debugger from BionicINS8060
2023-09-18 [BionicZ8691] Fixup for Z86C91
2023-09-18 [BionicZ8691] Add i8251 USART emulator
2023-09-18 [BionicZ8691] Support interrupt acknowledge
2023-11-26 [BionicZ8800] Add Z88C00 UART handler
2023-11-26 [BionicSCN2650] Copy debugger from BionicZ8800
2023-11-26 [CybordHD6309] Update to libasm 1.6.32 and libcli 1.3.0
2023-11-26 [BionicZ8691] Add Z8 SIO Handler and sample sources
2023-11-26 [IM6100] Add IM6100 pin out
2023-11-26 [TMS7000] Add TMS7000 pin out
2023-11-26 [BionicZ8800] Add example sources
2023-11-26 [BionicZ8800] Add integer arithmetic routines
2023-11-26 [BionicZ8691] Add Z8671 BASIC ROM
    - Add 'M' (ROM area) command to write protect only from CPU.
    - Z8671 BASIC ROM
    https://hc-ddr.hucki.net/wiki/doku.php/elektronik/z8671
    http://www.armory.com/~rstevew/Public/Micros/Z8/Z8671-BASIC/Z8671-BASIC_ROM_Main.htm
2023-11-26 [TMS9981] Add TMS9981 pin out
2023-11-26 [BionicZ8800] Add break point command
2023-11-26 [BionicSCN2650] Add exmple sources
2023-11-26 [BionicZ8800] Add halt check
2023-11-26 [BionicZ8691] Add Upload command
2023-11-26 [BionicZ8691] Add Break point command
2023-11-26 [BionicZ8691] Add halt check
2023-11-26 [BionicP8085] Add Upload command
2023-11-26 [BionicZ8691] Add integer mandelbrot
2023-11-26 [BionicBase] Add DC-DC Converter for +15V
2023-11-26 [BionicP8085] Add integer mandelbrot
2023-11-26 [BionicP8085] Add break point command
2023-12-05 [BionicTLCS90] Copy debugger from BionicSCN2650
2023-12-06 [BionicTLCS90] Add TLCS90 UART Handler
2023-12-06 [BionicTLCS90] Add integer mandelbrot
2023-12-06 [BionicTLCS90] Fixup for TLCS90
2023-12-07 [BionicTLCS90] Improve bus cycle pattern match
2023-12-07 [BionicF3850] Copy debugger from BionicTLCS90
2023-12-22 [BionicF3850] Add example sources
2023-12-22 [BionicF3850] Add 16-bit integer arithmenitc routines
2023-12-22 Remove Teensy 3.5
2023-12-29 Split CyborgHD6309E and CyborgZ84C00 repositories
    https://github.com:tgtakaoka/CyborgHD6309E.git
    https://github.com:tgtakaoka/CyborgZ84C00.git
    Using git subtree command.
    See https://medium.com/@jeevansathisocial/extract-subdirectory-from-git-repository-without-losing-history-3de8aed359a4
2024-02-20 Rename CheatSheet to pinout
2024-02-20 [CDP1802] Move schematics directory
2024-02-21 [MC68HC11D] Move schematics directory
2024-02-21 [MC6809] Move schematics directory
2024-02-21 [MC6801] Move schematics directory
2024-02-21 [MC6800] Move schematics directory
2024-02-21 [MC6802] Move schematics directory
2024-02-21 [INS8060] Move schematics directory
2024-02-21 [TMP90C802] Move schematics directory
2024-02-21 Remove mezzanine board schematics
2024-02-21 [TMS32010] Move schematics directory
2024-02-21 [TMS99105] Move schematics directory
2024-02-21 [TMS9981] Add TMS9981 bionic prototype
2024-02-21 [P8048] Move schematics directory
2024-02-21 [Z80] Move schematics directory
2024-02-21 [Z8800] Move schematics directory
2024-02-21 [IM6100] Add IM6100 Bionic Prototype
2024-02-21 [MOS6502] Move schematics directory
2024-02-21 [TMS7000] Add TMS7000 Bionic prototype
2024-02-21 [P8085] Move schematics directory
2024-02-21 [NSC800] Move schematics directory
2024-02-21 [Z8001] Move schematics directory
2024-02-21 [TMS9995] Move schematics directory
2024-03-01 [Debugger] Add unified debugger base
2024-03-01 [F3850] Unify debugger
2024-03-03 [INS8070] Unify debugger
2024-03-05 [TLCS90] Unify debugger
2024-03-05 [MC6801] Unify debugger
2024-03-05 [MC146805E] Unify debugger
2024-03-05 [MC6800] Unify debugger
2024-03-05 [MC6809] Unify debuffer
2024-03-05 [Z8800] Unify debugger
2024-03-05 [MC68HC11D] Unify debugger
2024-03-06 [WIP] Add GitHub CI
2024-03-21 [CDP1802] Remove HC126
2024-03-21 [INS8060] Remove HC126
2024-03-21 [MC146805E2] Remove HC126
2024-03-21 [MC6801] Remove HC126
2024-03-21 [MC6802] Remove HC126
2024-03-21 [MC6809E] Remove HC126
2024-03-21 [MOS6502] Remove HC126
2024-03-21 [P8085] Remove HC126
